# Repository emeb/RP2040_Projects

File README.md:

# RP2040_Projects
A collection of random projects based on the Raspberry Pi RP2040 MCU

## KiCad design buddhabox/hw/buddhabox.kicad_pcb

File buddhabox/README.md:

# buddhabox

A battery-powered RP2040-based audio noisemaker built into an inexpensive and readily-available portable case.

## What is it?

I came across these inexpensive Buddhist prayer chanting boxes after learning about the [Buddha Machine]([FM3 - Wikipedia](https://en.wikipedia.org/wiki/FM3#Buddha_Machine)) ambient loop player. The original Buddha Machines are no longer made but these prayer chanters are readily available from many sources and I immediately imagined repurposing them with customized loops. To that end, this project is a small PCB that exactly matches the original electronics with an RP2040, USB, flash memory and PWM driver, along with a single button to select which loop to play.

## Case

The case (as shown above) contains a small 4-ohm speaker, molded 2-cell AAA battery holder and slots for the power jack, 3.5mm mono headphone and power / volume thumbwheel. It is a 2-part clamshell with 4 self-tapping philips-head screws. There's a mold flashing where a button hole was filled in.

## Factory Driver Board

As originally built, the driver electronics is a small single-layer fenolic resin board with a chip-on-board (COB) "blob" IC that contains a single loop of prayer chanting which plays immediately on power-up. There is a small combined thumbwheel volume control / power switch similar to those found on old transistor radios, a barrel-type power jack and a mono 3.5mm audio jack, as well as wire connections to the speaker and battery holder. The board is held in place by two self-tapping screws and has drilled connections and mounting holes for a button to match the location of the filled hole in the case.

## Replacement Board

The new buddhabox board comprises an RP2040 MCU with micro USB connector, 4MB QSPI flash for code and sample storage, a single-channel PWM driver amp, button, LED and combined volume & power thumbwheel. The board shape matches the factory board and mounts with the same screws, but hole for the original power jack is unused, the hole for the headphone jack must be widened for the USB jack and the filled hole for the side button must be carved out. Additional buttons for reset and boot mode and connectors for serial TX/RX and SWD programming are provided on the board to facilitate development.

### Design Materials

[Schematic PDF](./doc/schematic.pdf)

[PCB at OSHPark](https://oshpark.com/shared_projects/EMfbYZtG)

[BOM](./hw/buddhabox_BOM.ods)

### Caveats

Although the board design works, there are a few "gotchas" to be aware of:

1. The circuit includes an option to power the board from the USB port which doesn't work properly - I'd assumed that the U1 battery boost regulator could regulate when driven with 5V USB power, but it doesn't regulate in that condition and merely passes the 5V straight thru to the 3.3V rail. To prevent this lift the VBUS leg of D1.

2. The back of the speaker rests immediately under the lower edge of the PCB and could short out some of the header connectors. To prevent this trim the connector leads flush with the back of the board and insulate the back of the speaker with tape.

3. The power/volume thumbwheel is a bit hard to find. I bought mine here: [Radio Volume Controls at AliExpress](https://www.aliexpress.us/item/3256801655864095.html)

## Firmware

The included firmware provides a IRQ-driven 11kSPS 8-bit PWM output that can be driven with loops of audio or synthesized sources selected sequentially by pressing the external button. As initially configured there are four loops derived from various musical cuts, followed by several tone and noise generators. Code can be loaded via SWD or USB, but in either approach the case must be opened to access the boot button and/or SWD connections.

## Going Further

Future revisions of the board design should address the items mentioned in "Caveats" above. It might also be interesting to replace the PWM output with an I2S speaker driver for "higher fidelity".

Firmware could be augmented to automatically detect when USB is attached and allow downloading new loops without fully reloading the entire code base.

## Related Projects

[Aleatorium](https://github.com/jonbro/aleatorium/) A fork/extension with better audio output circuits and a scriptable synth that includes an editor. Definitely worth a look.

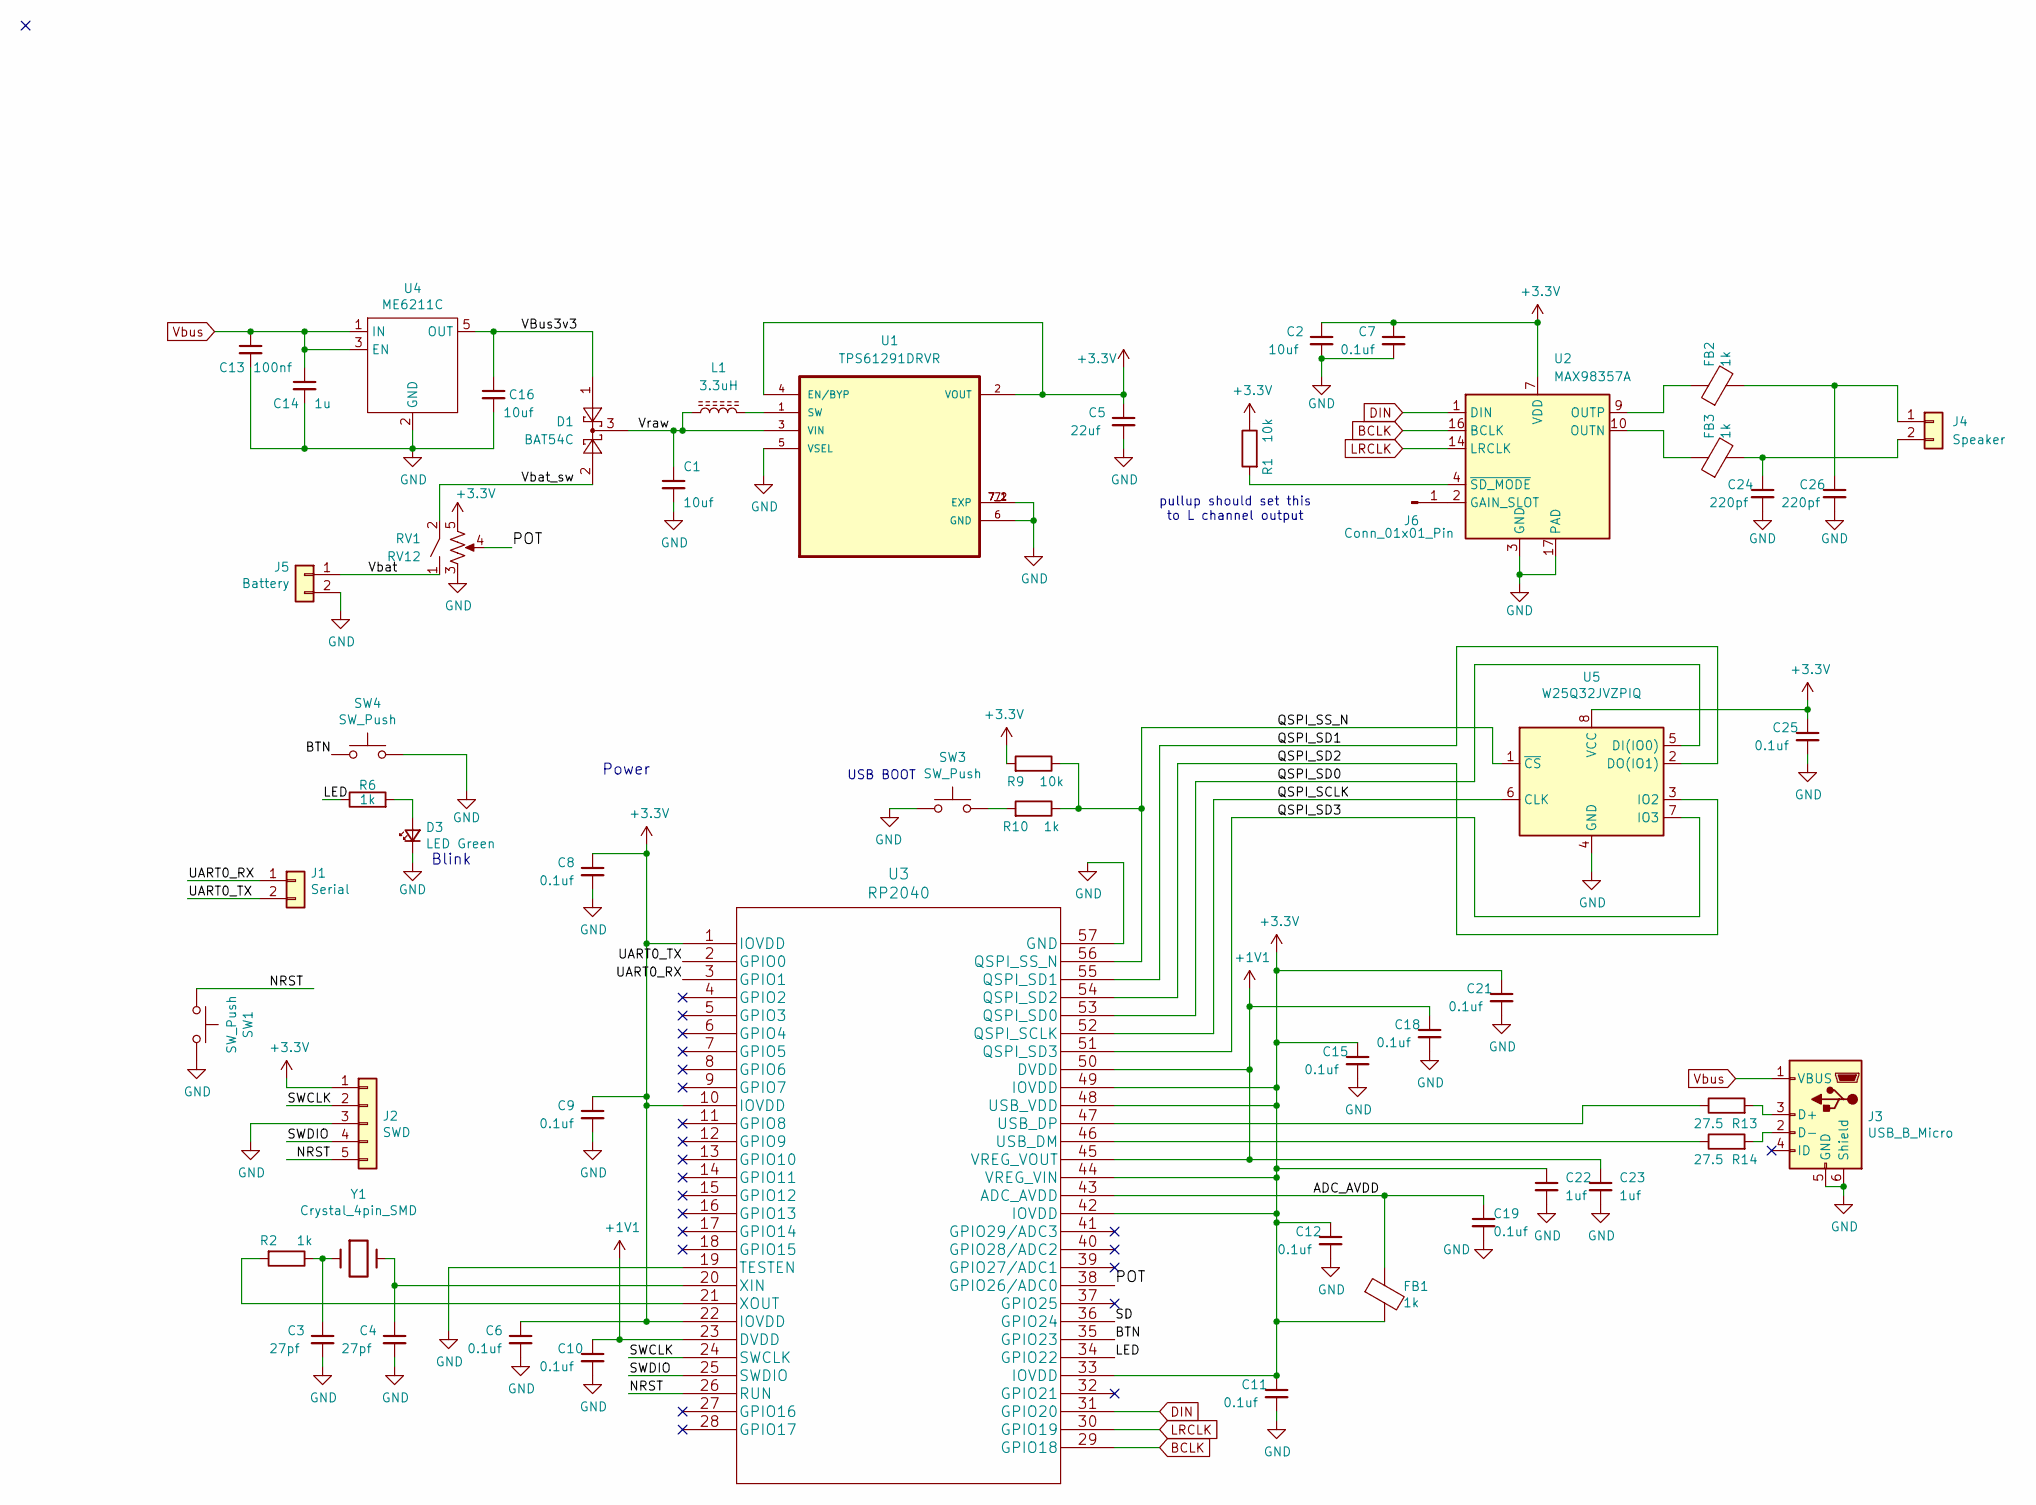
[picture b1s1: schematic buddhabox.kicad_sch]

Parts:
C1: 10uf; C_0805_2012Metric
C2, C16: 10uf; C_0402_1005Metric
C3, C4: 27pf; C_0402_1005Metric
C5: 22uf; C_1210_3225Metric
C6, C7, C8, C9, C10, C11, C12, C15, C18, C19, C21, C25: 0.1uf; C_0402_1005Metric
C13: 100nf; C_0402_1005Metric
C14: 1u; C_0402_1005Metric
C22, C23: 1uf; C_0402_1005Metric
C24, C26: 220pf; C_0402_1005Metric
D1: BAT54C; SOT-23
D3: LED Green; LED_0603_1608Metric
FB1, FB2, FB3: 1k; L_0402_1005Metric
J1: Serial; PinHeader_1x02_P2.54mm_Vertical
J2: SWD; PinHeader_1x05_P2.54mm_Vertical
J3: USB_B_Micro; USB_Micro-B_Amphenol_10103594-0001LF_Horizontal
J4: Speaker; PinHeader_1x02_P2.54mm_Vertical
J5: Battery; PinHeader_1x02_P2.54mm_Vertical
J6: Conn_01x01_Pin
L1: 3.3uH; L_Taiyo-Yuden_MD-2020
R1, R9: 10k; R_0402_1005Metric
R2, R6, R10: 1k; R_0402_1005Metric
R13, R14: 27.5; R_0402_1005Metric
RV1: RV12
SW1, SW3: SW_Push; SW_Push_1P1T_NO_CK_KMR2
SW4: SW_Push; SW_Tactile_SPST_Angled_PTS645Vx83-2LFS
U1: TPS61291DRVR; SON65P200X200X80-7N
U2: MAX98357A; TQFN-16-1EP_3x3mm_P0.5mm_EP1.23x1.23mm
U3: RP2040; LCSC C2040
U4: ME6211C; SOT-23-5
U5: W25Q32JVZPIQ; WSON-8-1EP_6x5mm_P1.27mm_EP3.4x4.3mm; LCSC C571260
Y1: Crystal_4pin_SMD; Crystal_SMD_3225-4Pin_3.2x2.5mm; LCSC C9002

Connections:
+1V1: C10.1, C18.1, C23.1, U3.23 (DVDD), U3.45 (VREG_VOUT), U3.50 (DVDD)
+3.3V: C2.1, C5.1, C6.1, C7.1, C8.1, C9.1, C11.1, C12.1, C15.1, C21.1, C22.1, C25.1, FB1.2, J2.1, R1.1, R9.2, RV1.5, U1.2 (VOUT), U1.4 (EN/BYP), U2.7 (VDD), U2.8 (VDD), U3.1 (IOVDD), U3.10 (IOVDD), U3.22 (IOVDD), U3.33 (IOVDD), U3.42 (IOVDD), U3.44 (VREG_VIN), U3.48 (USB_VDD), U3.49 (IOVDD), U5.8 (VCC)
/ADC_AVDD: C19.1, FB1.1, U3.43 (ADC_AVDD)
/BTN: SW4.2, U3.35 (GPIO23)
/LED: R6.1, U3.34 (GPIO22)
/NRST: J2.5, SW1.1, U3.26 (RUN)
/POT: RV1.4, U3.38 (GPIO26/ADC0)
/QSPI_SCLK: U3.52 (QSPI_SCLK), U5.6 (CLK)
/QSPI_SD0: U3.53 (QSPI_SD0), U5.5 (DI(IO0))
/QSPI_SD1: U3.55 (QSPI_SD1), U5.2 (DO(IO1))
/QSPI_SD2: U3.54 (QSPI_SD2), U5.3 (IO2)
/QSPI_SD3: U3.51 (QSPI_SD3), U5.7 (IO3)
/QSPI_SS_N: R9.1, R10.1, U3.56 (QSPI_SS_N), U5.1 (~CS)
/SD: U3.36 (GPIO24)
/SWCLK: J2.2, U3.24 (SWCLK)
/SWDIO: J2.4, U3.25 (SWDIO)
/UART0_RX: J1.1, U3.3 (GPIO1)
/UART0_TX: J1.2, U3.2 (GPIO0)
/VBus3v3: C16.1, D1.1, U4.5 (OUT)
/Vbat: J5.1, RV1.1
/Vbat_sw: D1.2, RV1.2
/Vraw: C1.1, D1.3, L1.1, U1.3 (VIN)
BCLK: U2.16 (BCLK), U3.29 (GPIO18)
DIN: U2.1 (DIN), U3.31 (GPIO20)
GND: C1.2, C2.2, C3.2, C4.2, C5.2, C6.2, C7.2, C8.2, C9.2, C10.2, C11.2, C12.2, C13.2, C14.2, C15.2, C16.2, C18.2, C19.2, C21.2, C22.2, C23.2, C24.2, C25.2, C26.2, D3.1 (K), J2.3, J3.5 (GND), J3.6 (Shield), J5.2, RV1.3, SW1.2, SW3.2, SW4.1, U1.5 (VSEL), U1.6 (GND), U1.7 (EXP), U1.7_1 (EXP), U1.7_2 (EXP), U2.3 (GND), U2.11 (GND), U2.15 (GND), U2.17 (PAD), U3.19 (TESTEN), U3.57 (GND), U4.2 (GND), U5.4 (GND)
LRCLK: U2.14 (LRCLK), U3.30 (GPIO19)
unnamed: C3.1, R2.1, Y1.1
unnamed: D3.2 (A), R6.2
unnamed: J3.3 (D+), R13.2
unnamed: J3.2 (D-), R14.2
unnamed: C26.1, FB2.2, J4.1
unnamed: C24.1, FB3.2, J4.2
unnamed: J6.1, U2.2 (GAIN_SLOT)
unnamed: R10.2, SW3.1
unnamed: L1.2, U1.1 (SW)
unnamed: FB3.1, U2.10 (OUTN)
unnamed: FB2.1, U2.9 (OUTP)
unnamed: R1.2, U2.4 (~SD_MODE)
unnamed: R14.1, U3.46 (USB_DM)
unnamed: R13.1, U3.47 (USB_DP)
unnamed: C4.1, U3.20 (XIN), Y1.3
unnamed: R2.2, U3.21 (XOUT)
Vbus: C13.1, C14.1, J3.1 (VBUS), U4.1 (IN), U4.3 (EN)

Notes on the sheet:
pullup should set this to L channel output
USB BOOT
Blink
Power

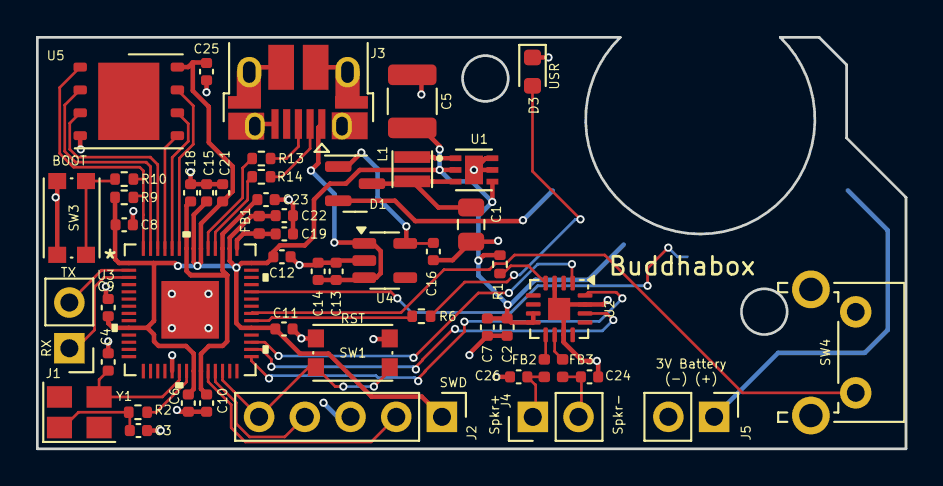
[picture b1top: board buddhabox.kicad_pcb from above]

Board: 2 copper layers, 48.3 x 22.9 mm, 52 parts (1 on the bottom side), 41 nets.

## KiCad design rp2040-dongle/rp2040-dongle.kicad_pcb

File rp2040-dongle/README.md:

This is a small 'dongle' sized RP2040 device with an EYESPI FPC
connector compatible with Adafruit devices.

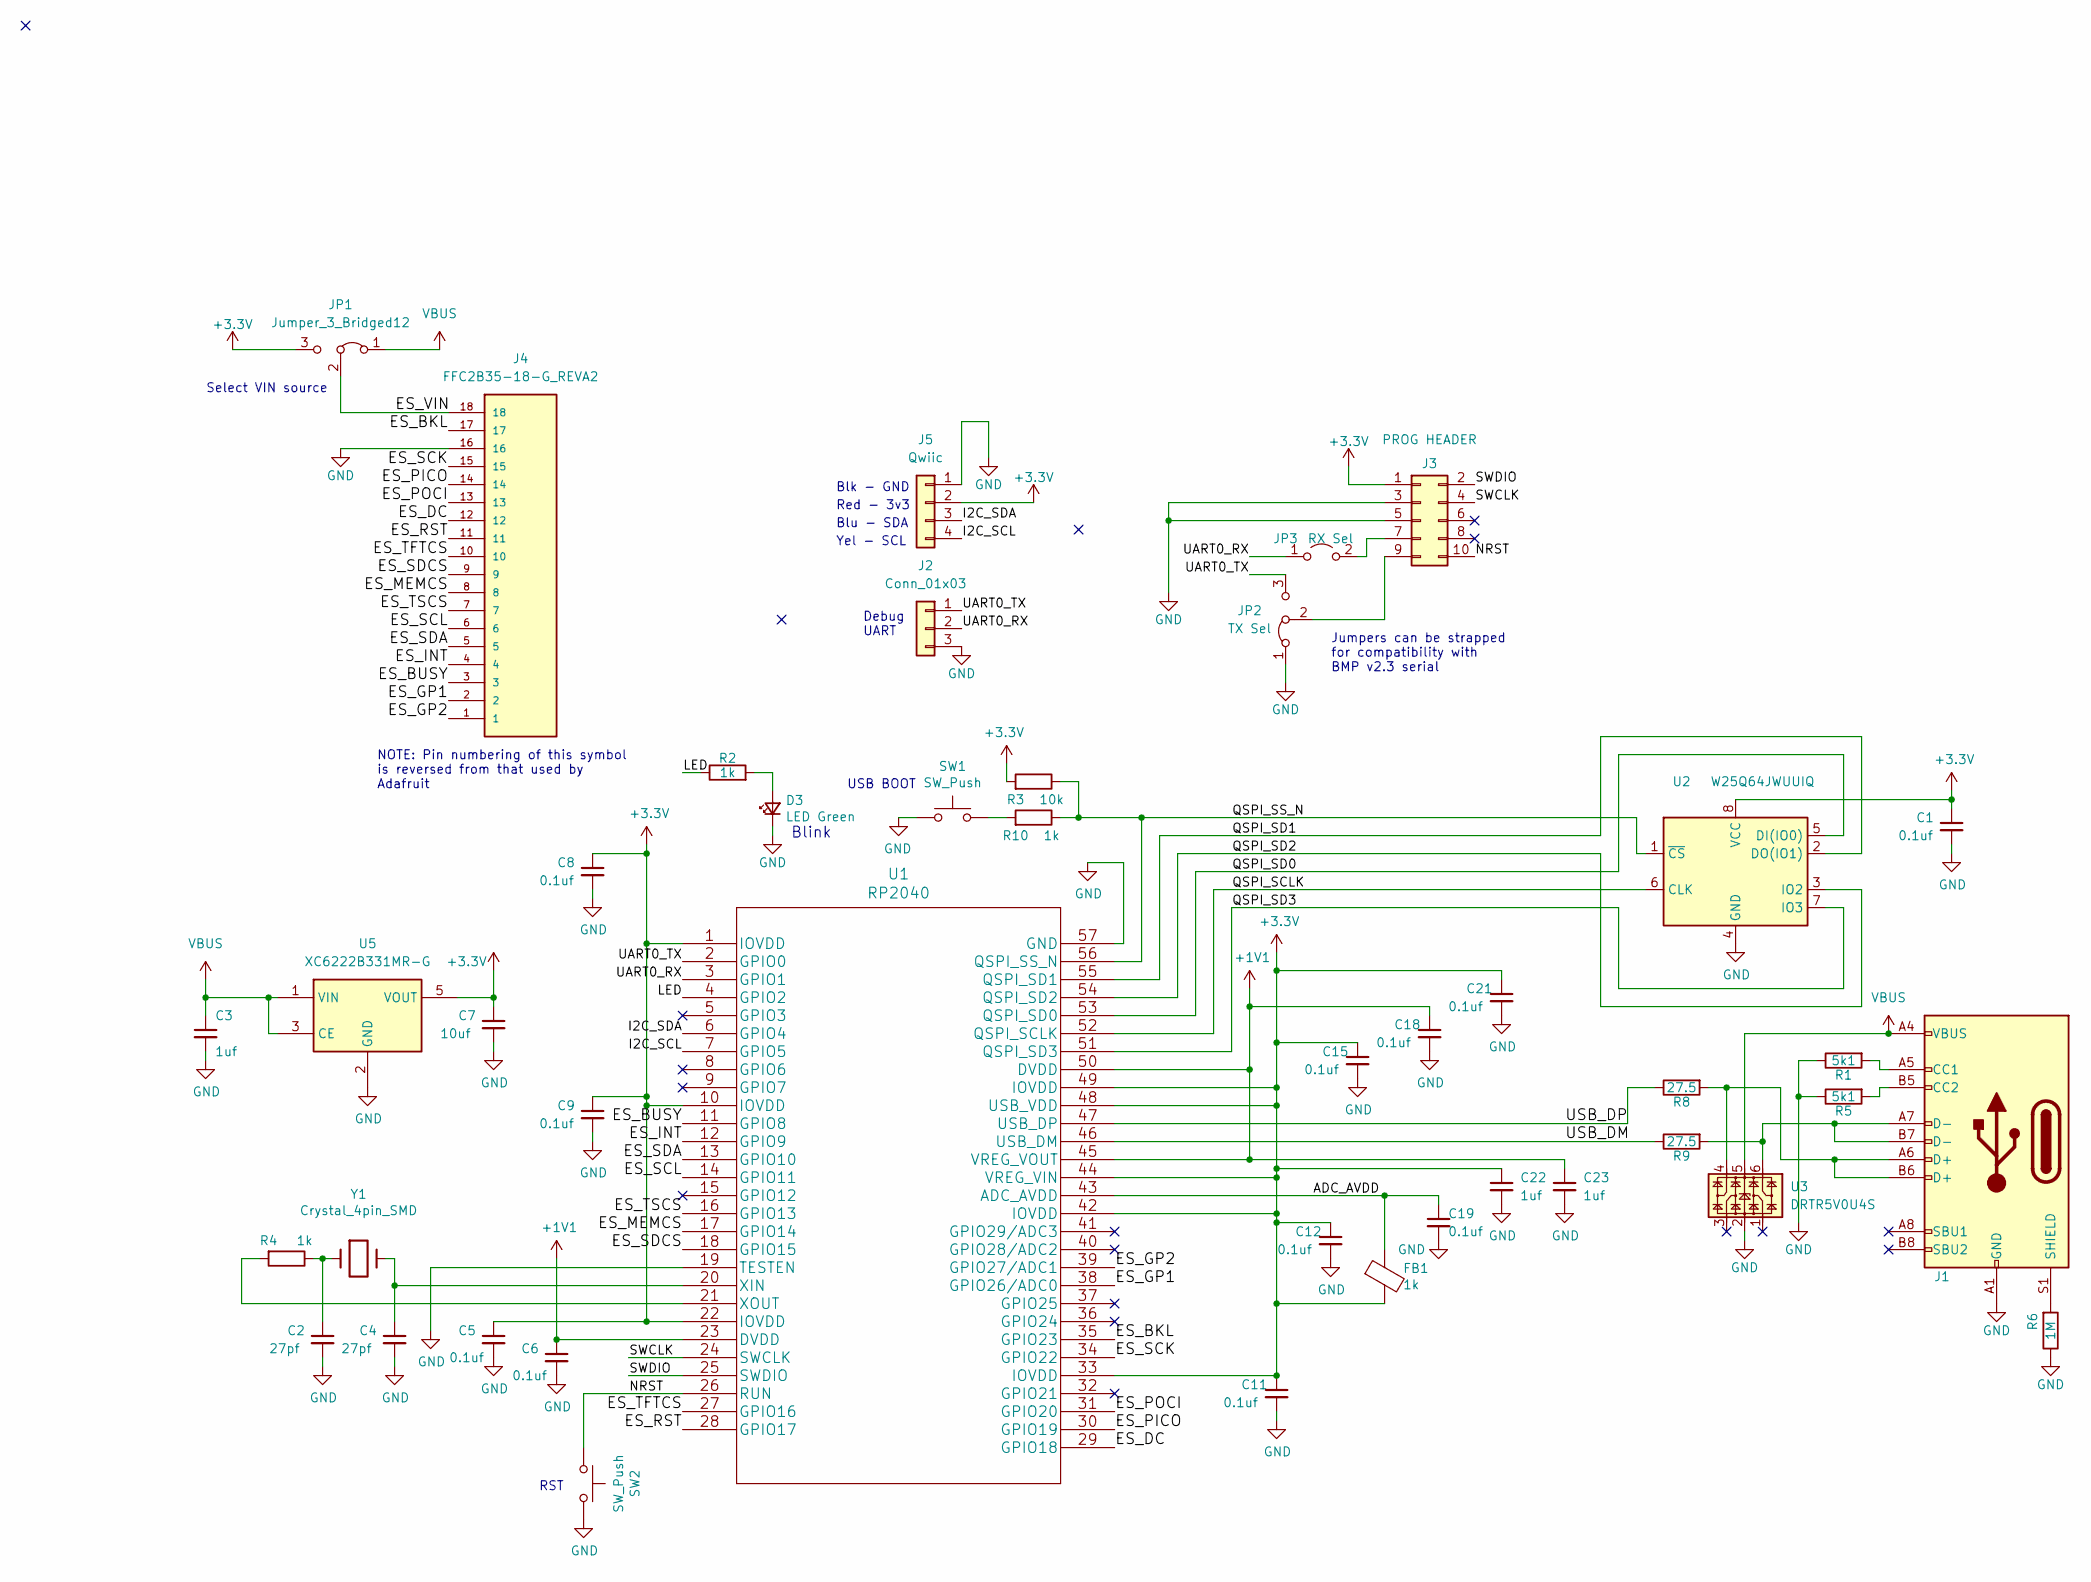
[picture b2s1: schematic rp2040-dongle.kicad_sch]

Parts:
C1, C5, C6, C8, C9, C11, C12, C15, C18, C19, C21: 0.1uf; C_0402_1005Metric
C2, C4: 27pf; C_0402_1005Metric
C3, C22, C23: 1uf; C_0402_1005Metric
C7: 10uf; C_0805_2012Metric
D3: LED Green; LED_0603_1608Metric
FB1: 1k; L_0402_1005Metric
J1: USB_C_Receptacle_USB2.0; USB_C_Receptacle_HRO_TYPE-C-31-M-12
J2: Conn_01x03; PinHeader_1x03_P2.54mm_Vertical
J3: PROG HEADER; PinHeader_2x05_P1.27mm_Vertical_SMD
J4: FFC2B35-18-G_REVA2; GCT_FFC2B35-18-G_REVA2; PARTREV A2
J5: Qwiic; PinHeader_1x04_P1.27mm_Vertical
JP1: Jumper_3_Bridged12; SolderJumper-3_P1.3mm_Bridged12_RoundedPad1.0x1.5mm
JP2: TX Sel; SolderJumper-3_P1.3mm_Bridged12_RoundedPad1.0x1.5mm
JP3: RX Sel; SolderJumper-2_P1.3mm_Open_RoundedPad1.0x1.5mm
R1, R5: 5k1; R_0402_1005Metric
R2, R4, R10: 1k; R_0402_1005Metric
R3: 10k; R_0402_1005Metric
R6: 1M; R_0402_1005Metric
R8, R9: 27.5; R_0402_1005Metric
SW1, SW2: SW_Push; SW_SPST_PTS815
U1: RP2040
U2: W25Q64JWUUIQ; USON-8_4x3
U3: DRTR5V0U4S; SOT-363_SC-70-6
U5: XC6222B331MR-G; SOT-23-5
Y1: Crystal_4pin_SMD; Crystal_SMD_3225-4Pin_3.2x2.5mm

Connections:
+1V1: C6.1, C18.1, C23.1, U1.23 (DVDD), U1.45 (VREG_VOUT), U1.50 (DVDD)
+3.3V: C1.1, C5.1, C7.1, C8.1, C9.1, C11.1, C12.1, C15.1, C21.1, C22.1, FB1.2, J3.1, J5.2, JP1.3 (B), R3.2, U1.1 (IOVDD), U1.10 (IOVDD), U1.22 (IOVDD), U1.33 (IOVDD), U1.42 (IOVDD), U1.44 (VREG_VIN), U1.48 (USB_VDD), U1.49 (IOVDD), U2.8 (VCC), U5.5 (VOUT)
/ADC_AVDD: C19.1, FB1.1, U1.43 (ADC_AVDD)
/ES_BKL: J4.17, U1.35 (GPIO23)
/ES_BUSY: J4.3, U1.11 (GPIO8)
/ES_DC: J4.12, U1.29 (GPIO18)
/ES_GP1: J4.2, U1.38 (GPIO26/ADC0)
/ES_GP2: J4.1, U1.39 (GPIO27/ADC1)
/ES_INT: J4.4, U1.12 (GPIO9)
/ES_MEMCS: J4.8, U1.17 (GPIO14)
/ES_PICO: J4.14, U1.30 (GPIO19)
/ES_POCI: J4.13, U1.31 (GPIO20)
/ES_RST: J4.11, U1.28 (GPIO17)
/ES_SCK: J4.15, U1.34 (GPIO22)
/ES_SCL: J4.6, U1.14 (GPIO11)
/ES_SDA: J4.5, U1.13 (GPIO10)
/ES_SDCS: J4.9, U1.18 (GPIO15)
/ES_TFTCS: J4.10, U1.27 (GPIO16)
/ES_TSCS: J4.7, U1.16 (GPIO13)
/ES_VIN: J4.18, JP1.2 (C)
/I2C_SCL: J5.4, U1.7 (GPIO5)
/I2C_SDA: J5.3, U1.6 (GPIO4)
/LED: R2.1, U1.4 (GPIO2)
/NRST: J3.10, SW2.1, U1.26 (RUN)
/QSPI_SCLK: U1.52 (QSPI_SCLK), U2.6 (CLK)
/QSPI_SD0: U1.53 (QSPI_SD0), U2.5 (DI(IO0))
/QSPI_SD1: U1.55 (QSPI_SD1), U2.2 (DO(IO1))
/QSPI_SD2: U1.54 (QSPI_SD2), U2.3 (IO2)
/QSPI_SD3: U1.51 (QSPI_SD3), U2.7 (IO3)
/QSPI_SS_N: R3.1, R10.1, U1.56 (QSPI_SS_N), U2.1 (~CS)
/SWCLK: J3.4, U1.24 (SWCLK)
/SWDIO: J3.2, U1.25 (SWDIO)
/UART0_RX: J2.2, JP3.1 (A), U1.3 (GPIO1)
/UART0_TX: J2.1, JP2.3 (B), U1.2 (GPIO0)
/USB_DM: R9.1, U1.46 (USB_DM)
/USB_DP: R8.1, U1.47 (USB_DP)
GND: C1.2, C2.2, C3.2, C4.2, C5.2, C6.2, C7.2, C8.2, C9.2, C11.2, C12.2, C15.2, C18.2, C19.2, C21.2, C22.2, C23.2, D3.1 (K), J1.A1 (GND), J1.A12 (GND), J1.B1 (GND), J1.B12 (GND), J2.3, J3.3, J3.5, J4.16, J5.1, JP2.1 (A), R1.1, R5.1, R6.1, SW1.2, SW2.2, U1.19 (TESTEN), U1.57 (GND), U2.4 (GND), U3.2, U5.2 (GND)
unnamed: C4.1, U1.20 (XIN), Y1.3
unnamed: D3.2 (A), R2.2
unnamed: J1.A5 (CC1), R1.2
unnamed: J1.A7 (D-), J1.B7 (D-), R9.2, U3.6
unnamed: J1.B5 (CC2), R5.2
unnamed: J3.7, JP3.2 (B)
unnamed: J3.9, JP2.2 (C)
unnamed: J1.S1 (SHIELD), R6.2
unnamed: J1.A6 (D+), J1.B6 (D+), R8.2, U3.4
unnamed: R10.2, SW1.1
unnamed: R4.2, U1.21 (XOUT)
unnamed: C2.1, R4.1, Y1.1
VBUS: C3.1, J1.A4 (VBUS), J1.A9 (VBUS), J1.B4 (VBUS), J1.B9 (VBUS), JP1.1 (A), U3.5, U5.1 (VIN), U5.3 (CE)

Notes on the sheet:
Debug UART
NOTE: Pin numbering of this symbol is reversed from that used by Adafruit
Yel - SCL
Blu - SDA
Jumpers can be strapped for compatibility with BMP v2.3 serial
USB BOOT
Select VIN source
Blink
RST
Red - 3v3
Blk - GND

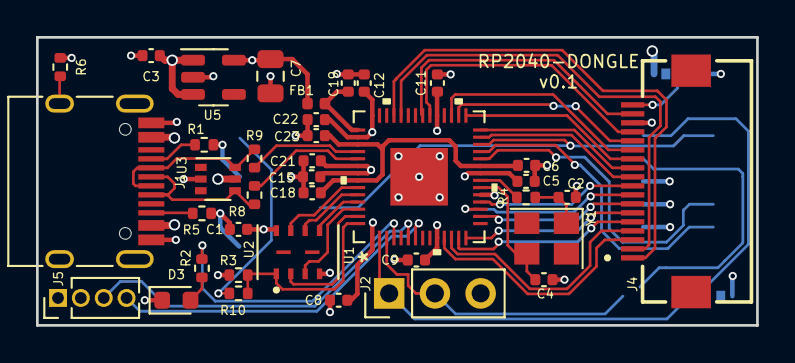
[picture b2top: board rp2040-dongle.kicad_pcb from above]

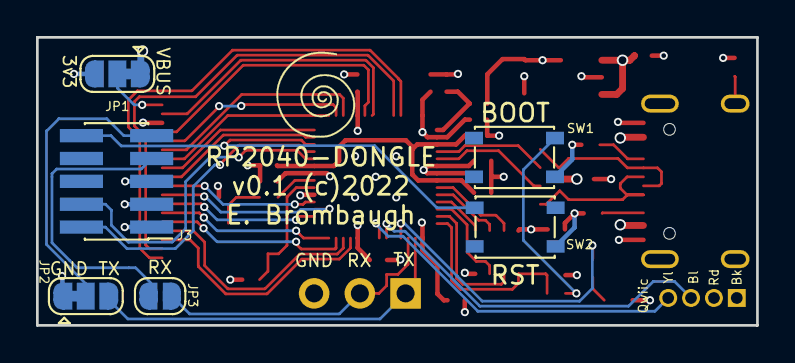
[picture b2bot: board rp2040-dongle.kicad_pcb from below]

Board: 4 copper layers, 40.0 x 16.0 mm, 44 parts (7 on the bottom side), 50 nets.

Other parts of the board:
Ref**: Val**; avatar_small

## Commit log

2022-12-01 Initial checkin of two in-process projects
2024-03-27 Updated with working board design and pictures.
2024-03-27 Add schematic link
2024-03-27 Added PCB link
2024-03-28 fix BOM link
2024-04-08 switch to i2s amp & added LDO to vbus
2024-04-14 updated schematic with lcsc part numbers

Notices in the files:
buddhabox/hw/buddhabox.kicad_pcb:
(c) 2022 E. Brombaugh
rp2040-dongle/rp2040-dongle.kicad_pcb:
v0.1 (c)2022
parts and their libraries:
Copyright 2021 Accelerated Designs. All rights reserved.
